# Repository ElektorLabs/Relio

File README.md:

# Relio
Relio : A Matter-Enabled Smart Controller for AC Appliances 
**Version:** v1  

## 📖 Project Overview

This project is a **Matter-enabled smart controller** built around the ESP32, with support for **relay control, environment sensing, energy monitoring, and occupancy detection**.  
It combines **hardware (KiCAD PCB design)** and **firmware (Arduino/C++ code)** into a single, ready-to-build system.

---

## 📂 Repository Structure

```

├── hardware/      # KiCAD PCB design files (schematics & layout)
└── src/           # Source code (Arduino / ESP-IDF compatible)

````

---

## ⚙️ Features

- **3x On/Off Lights** 💡  
  Controlled through a TCA9554 I²C expander.  
  - Always start **OFF** when powered up (safe startup).  
  - Exposed as **separate Matter endpoints**.  

- **Environmental Sensing (BME688)** 🌡️💧  
  - Temperature & Humidity exposed to Matter.  
  - Pressure & Gas Resistance logged to Serial for debugging.  

- **Energy Monitoring (BL0942)** ⚡  
  - Measures Voltage, Current, Power, Energy, Frequency.  
  - Data shown in Serial logs (Watts/Current can later be exposed to Matter).  

- **Occupancy Detection** 🚶‍♂️  
  - Uses TCA9554 pin 0 as input.  
  - HIGH = Occupied, LOW = Not Occupied.  
  - Reflected in Matter occupancy endpoint.  

- **Commissioning & Control** 🔐  
  - Commission into Matter fabric with QR/Manual code.  
  - BOOT button short press = toggle Light 1.  
  - BOOT button long press (5s) = decommission node.  

---

## 🧑‍💻 How the Code Works

- **Relay Control:**  
  `SWITCH1/2/3` booleans track relay states. Callbacks ensure Matter state and hardware (TCA9554 relays) stay in sync.  

- **BME688:**  
  Reads real temperature/humidity every 5s → updates Matter.  
  Pressure/gas logged for debugging but not exposed to Matter (yet).  

- **BL0942:**  
  Runs on `Serial1` (pins RX=4, TX=5, 4800 baud). Provides live power metrics to Serial monitor.  

- **Occupancy:**  
  Directly read from **TCA9554 pin 0**. When state changes, it’s pushed to the Matter controller and printed to Serial.  

---

## 🚀 Getting Started

1. Clone this repo:  
   ```bash
   git clone https://github.com/ElektorLabs/Relio.git
2. Open the src/ folder in Arduino IDE or PlatformIO.

3. Install dependencies:

   * [Espressif Matter Arduino](https://github.com/espressif/arduino-esp32)
   * [TCA9554 library](https://github.com/RobTillaart/TCA9554)
   * [BL0942 library](https://github.com/santerilindfors/BL0942)
   * [BME688 library](https://github.com/styropyr0/BME688)

4. Upload the code to your ESP32.

5. Use your Matter controller app to commission the device.

## 🛠️ Future Work

* Expose BL0942 **Power/Current** as native Matter attributes.
* Add Matter endpoints for **Pressure** & **Gas Resistance**.
* Add **configurable boot behavior** (restore last state vs always OFF).

---

## ⚠️ Disclaimer

This project is provided **as-is**, without warranty of any kind.
⚡ **Caution:** This project involves **mains-level voltages** (relays, energy metering).
Only experienced users should build or test this hardware. Always follow **electrical safety best practices** when working with AC-powered circuits.

The author is **not responsible** for any damage, injury, or loss caused by misuse of this code or hardware.

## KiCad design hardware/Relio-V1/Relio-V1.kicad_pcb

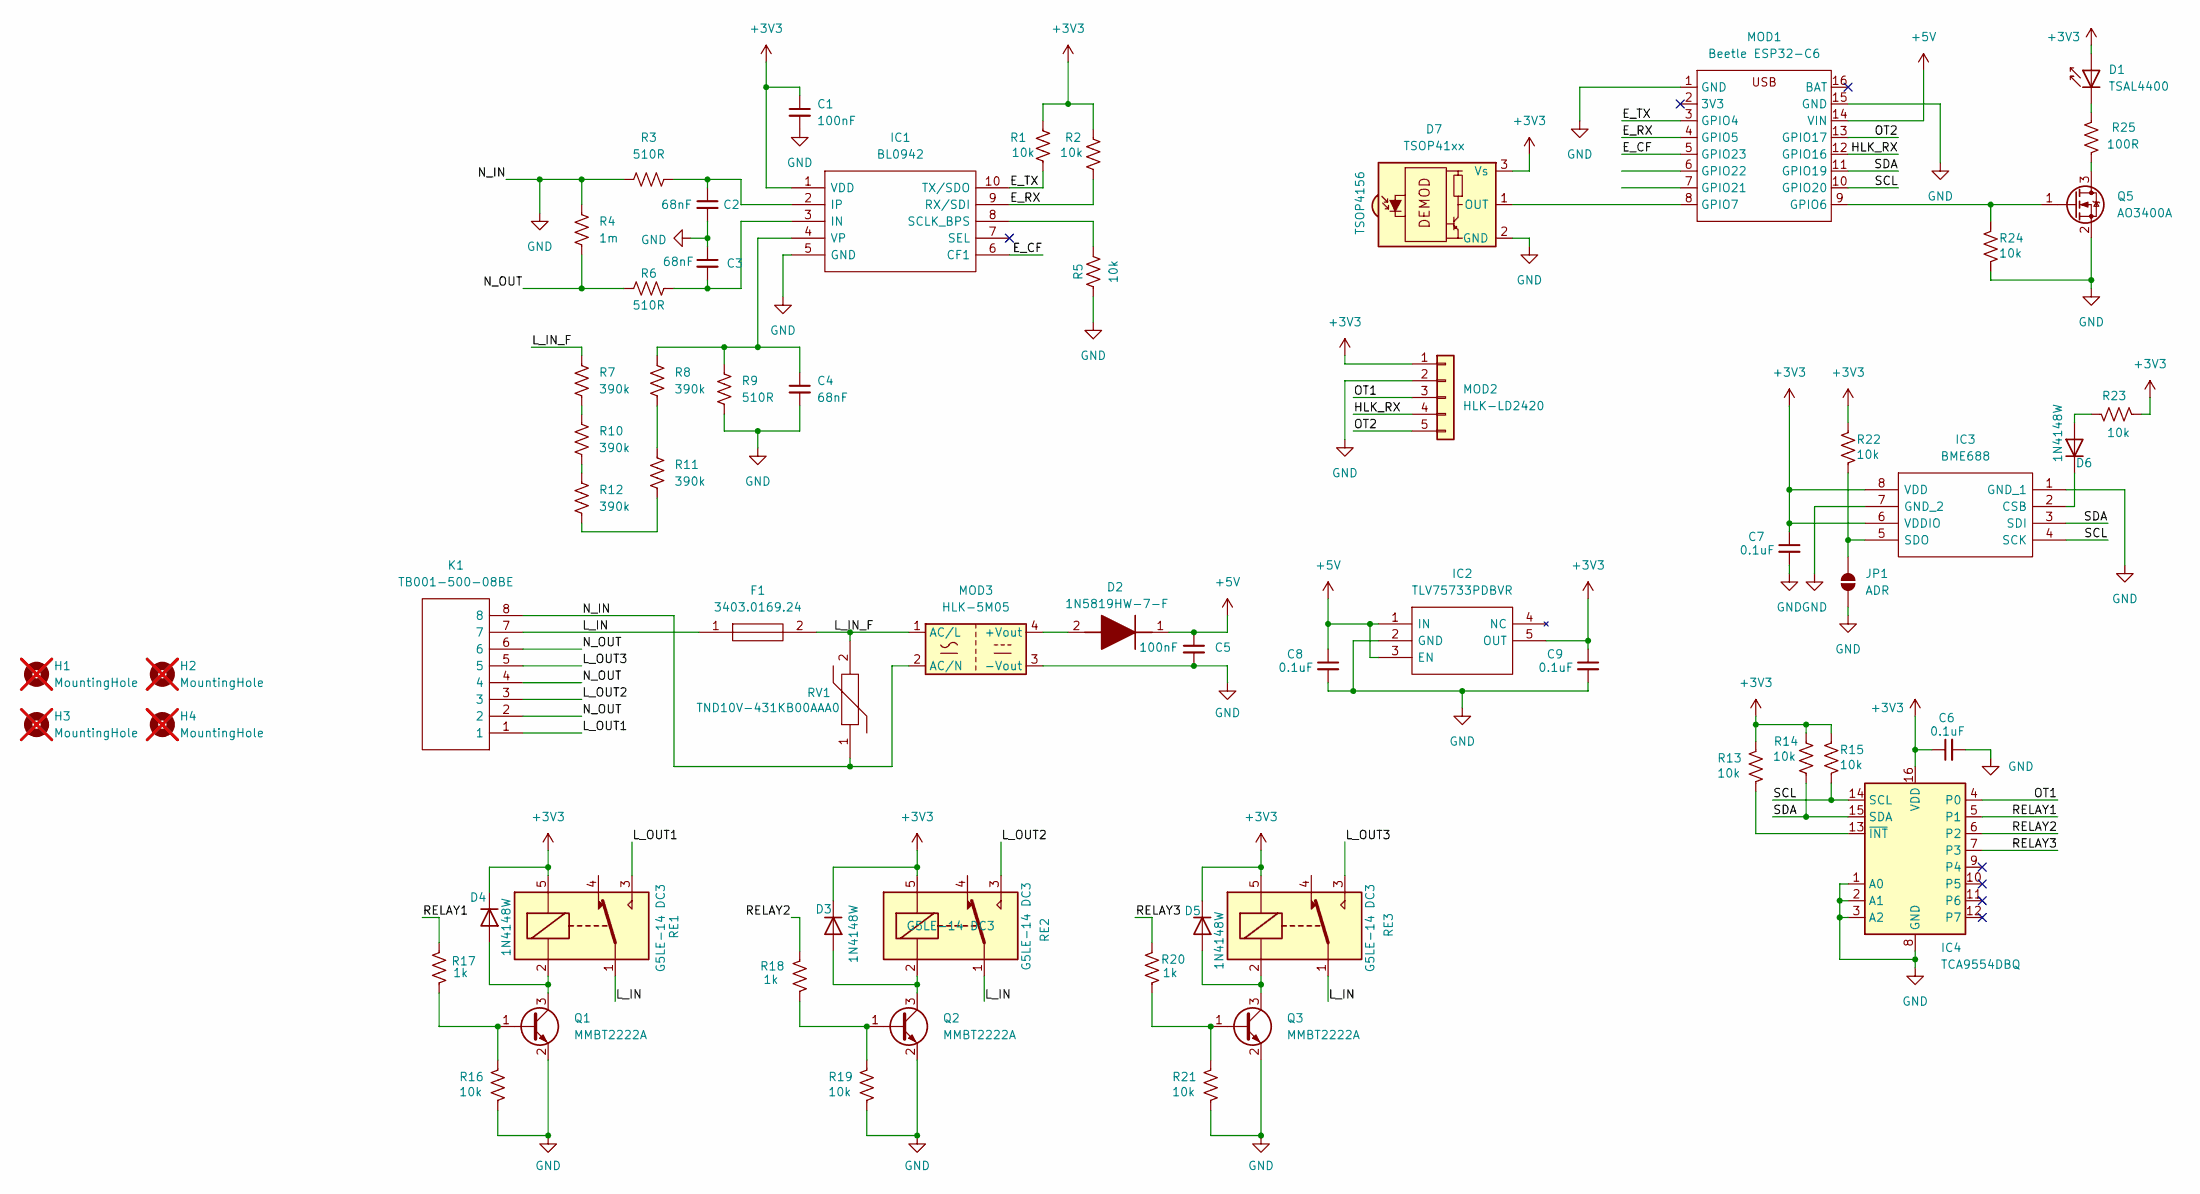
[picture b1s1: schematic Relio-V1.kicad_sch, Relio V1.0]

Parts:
C1, C5: 100nF; C_0805_2012Metric_Pad1.18x1.45mm_HandSolder; Manufacturer_Part_Number C0805C104M3RAC
C2, C3, C4: 68nF; C_0805_2012Metric_Pad1.18x1.45mm_HandSolder; Manufacturer_Part_Number C0805C683KARACAUTO
C6, C7, C8, C9: 0.1uF; C_0805_2012Metric_Pad1.18x1.45mm_HandSolder; Manufacturer_Part_Number C0805C104M3RAC
D1: TSAL4400; LED_D3.0mm_IRBlack; Manufacturer_Part_Number TSAL4400
D2: 1N5819HW-7-F; SOD3716X145N; Mouser Part Number 621-1N5819HW-F
D3, D4, D5, D6: 1N4148W; D_SOD-123; Manufacturer_Part_Number 1N4148W
D7: TSOP41xx; Vishay_MINICAST-3Pin; Manufacturer_Part_Number TSOP4156
F1: 3403.0169.24; FUSC10130X300N; Mouser Part Number 693-3403.0169.24
H1, H2, H3, H4: MountingHole; MountingHole_3.2mm_M3; not fitted
IC1: BL0942; SOP50P490X110-10N; Manufacturer_Part_Number BL0942
IC2: TLV75733PDBVR; SOT95P280X145-5N; Mouser Part Number 595-TLV75733PDBVR
IC3: BME688; Mouser Part Number 262-BME688
IC4: TCA9554DBQ; SSOP-16_3.9x4.9mm_P0.635mm; Manufacturer_Part_Number TCA9554DBQ
JP1: ADR; SolderJumper-2_P1.3mm_Open_RoundedPad1.0x1.5mm
K1: TB001-500-08BE; TB00150008BE; Mouser Part Number 490-TB001-500-08BE
MOD1: Beetle ESP32-C6; Manufacturer_Part_Number Beetle ESP32-C6
MOD2: HLK-LD2420; PinHeader_1x05_P2.54mm_Vertical; Manufacturer_Part_Number HLK-LD2420
MOD3: HLK-5M05; Converter_ACDC_Hi-Link_HLK-5Mxx; Manufacturer_Part_Number HLK-5M05
Q1, Q2, Q3: MMBT2222A; SOT-23; Manufacturer_Part_Number MMBT2222A
Q5: AO3400A; SOT-23; Manufacturer_Part_Number AO3400A
R1, R2, R5, R13, R14, R15, R16, R19, R21, R22, R23, R24: 10k; R_0805_2012Metric_Pad1.20x1.40mm_HandSolder; Manufacturer_Part_Number 0805W8J0103T5E
R3, R6, R9: 510R; R_0805_2012Metric_Pad1.20x1.40mm_HandSolder; Manufacturer_Part_Number SDR10EZPF5100
R4: 1m; R_1210_3225Metric
R7, R8, R10, R11, R12: 390k; R_2010_5025Metric; Manufacturer_Part_Number CRGCQ2010F390K
R17, R18, R20: 1k; R_0805_2012Metric_Pad1.20x1.40mm_HandSolder; Manufacturer_Part_Number 0805W8J0102T5E
R25: 100R; R_0805_2012Metric_Pad1.20x1.40mm_HandSolder; Manufacturer_Part_Number 0805S8J0101T5E
RE1, RE2, RE3: G5LE-14 DC3; Relay_SPDT_Omron-G5LE-1; Manufacturer_Part_Number G5LE-14 DC3
RV1: TND10V-431KB00AAA0; TND10V431KB00AAA0; Manufacturer_Part_Number TND10V-431KB00AAA0

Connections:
+3V3: C1.1, C6.1, C7.1, C9.1, D1.2 (A), D3.1 (K), D4.1 (K), D5.1 (K), D7.3 (Vs), IC1.1 (VDD), IC2.5 (OUT), IC3.6 (VDDIO), IC3.8 (VDD), IC4.16 (VDD), MOD2.1, R1.1, R2.1, R13.1, R14.1, R15.1, R22.1, R23.1, RE1.5, RE2.5, RE3.5
+5V: C5.1, C8.1, D2.1 (K), IC2.1 (IN), IC2.3 (EN), MOD1.14 (VIN)
/E_CF: IC1.6 (CF1), MOD1.5 (GPIO23)
/E_RX: IC1.9 (RX/SDI), MOD1.4 (GPIO5), R2.2
/E_TX: IC1.10 (TX/SDO), MOD1.3 (GPIO4), R1.2
/HLK_RX: MOD1.12 (GPIO16), MOD2.4
/L_IN: F1.1, K1.7, RE1.1, RE2.1, RE3.1
/L_IN_F: F1.2, MOD3.1 (AC/L), R7.2, RV1.2
/L_OUT1: K1.1, RE1.3
/L_OUT2: K1.3, RE2.3
/L_OUT3: K1.5, RE3.3
/N_OUT: K1.2, K1.4, K1.6, R4.1, R6.1
/OT1: IC4.4 (P0), MOD2.3
/OT2: MOD1.13 (GPIO17), MOD2.5
/RELAY1: IC4.5 (P1), R17.2
/RELAY2: IC4.6 (P2), R18.2
/RELAY3: IC4.7 (P3), R20.2
/SCL: IC3.4 (SCK), IC4.14 (SCL), MOD1.10 (GPIO20), R15.2
/SDA: IC3.3 (SDI), IC4.15 (SDA), MOD1.11 (GPIO19), R14.2
GND: C1.2, C2.2, C3.1, C4.2, C5.2, C6.2, C7.2, C8.2, C9.2, D7.2 (GND), IC1.5 (GND), IC2.2 (GND), IC3.1 (GND_1), IC3.7 (GND_2), IC4.1 (A0), IC4.2 (A1), IC4.3 (A2), IC4.8 (GND), JP1.1 (A), K1.8, MOD1.1 (GND), MOD1.15 (GND), MOD2.2, MOD3.2 (AC/N), MOD3.3 (-Vout), Q1.2 (E), Q2.2 (E), Q3.2 (E), Q5.2 (S), R3.1, R4.2, R5.1, R9.1, R16.2, R19.2, R21.2, R24.2, RV1.1
unnamed: D1.1 (K), R25.1
unnamed: D2.2 (A), MOD3.4 (+Vout)
unnamed: D3.2 (A), Q2.3 (C), RE2.2
unnamed: D4.2 (A), Q1.3 (C), RE1.2
unnamed: D5.2 (A), Q3.3 (C), RE3.2
unnamed: D6.2 (A), R23.2
unnamed: D6.1 (K), IC3.2 (CSB)
unnamed: D7.1 (OUT), MOD1.8 (GPIO7)
unnamed: C3.2, IC1.3 (IN), R6.2
unnamed: C2.1, IC1.2 (IP), R3.2
unnamed: IC1.8 (SCLK_BPS), R5.2
unnamed: C4.1, IC1.4 (VP), R8.2, R9.2
unnamed: IC3.5 (SDO), JP1.2 (B), R22.2
unnamed: IC4.13 (~INT), R13.2
unnamed: MOD1.9 (GPIO6), Q5.1 (G), R24.1
unnamed: Q1.1 (B), R16.1, R17.1
unnamed: Q2.1 (B), R18.1, R19.1
unnamed: Q3.1 (B), R20.1, R21.1
unnamed: Q5.3 (D), R25.2
unnamed: R10.1, R12.1
unnamed: R7.1, R10.2
unnamed: R11.1, R12.2
unnamed: R8.1, R11.2

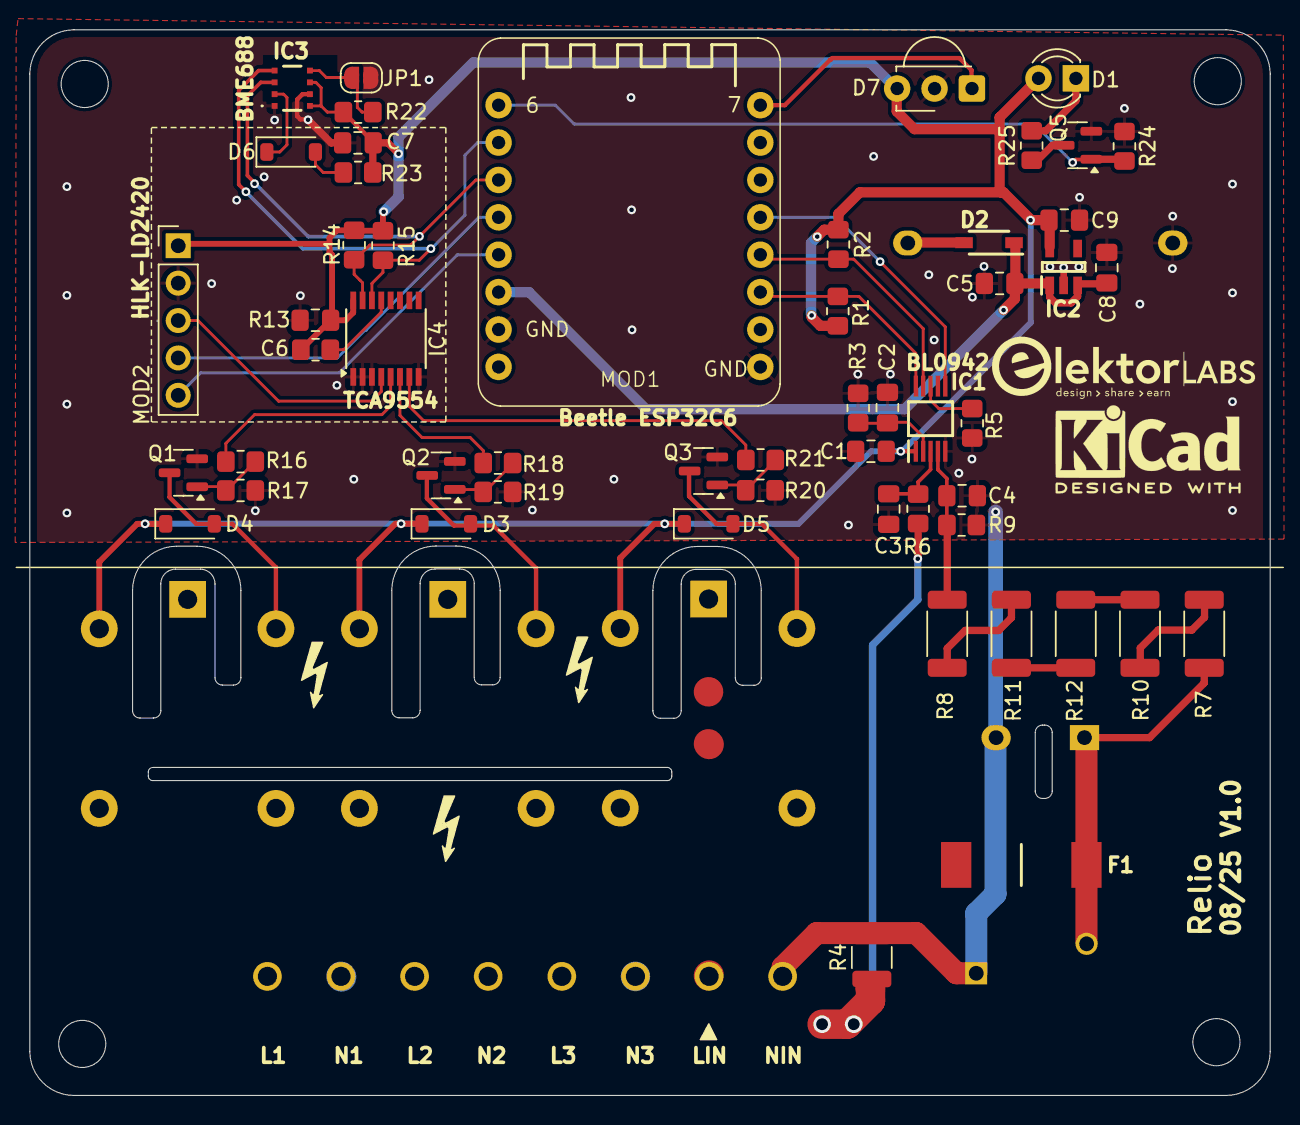
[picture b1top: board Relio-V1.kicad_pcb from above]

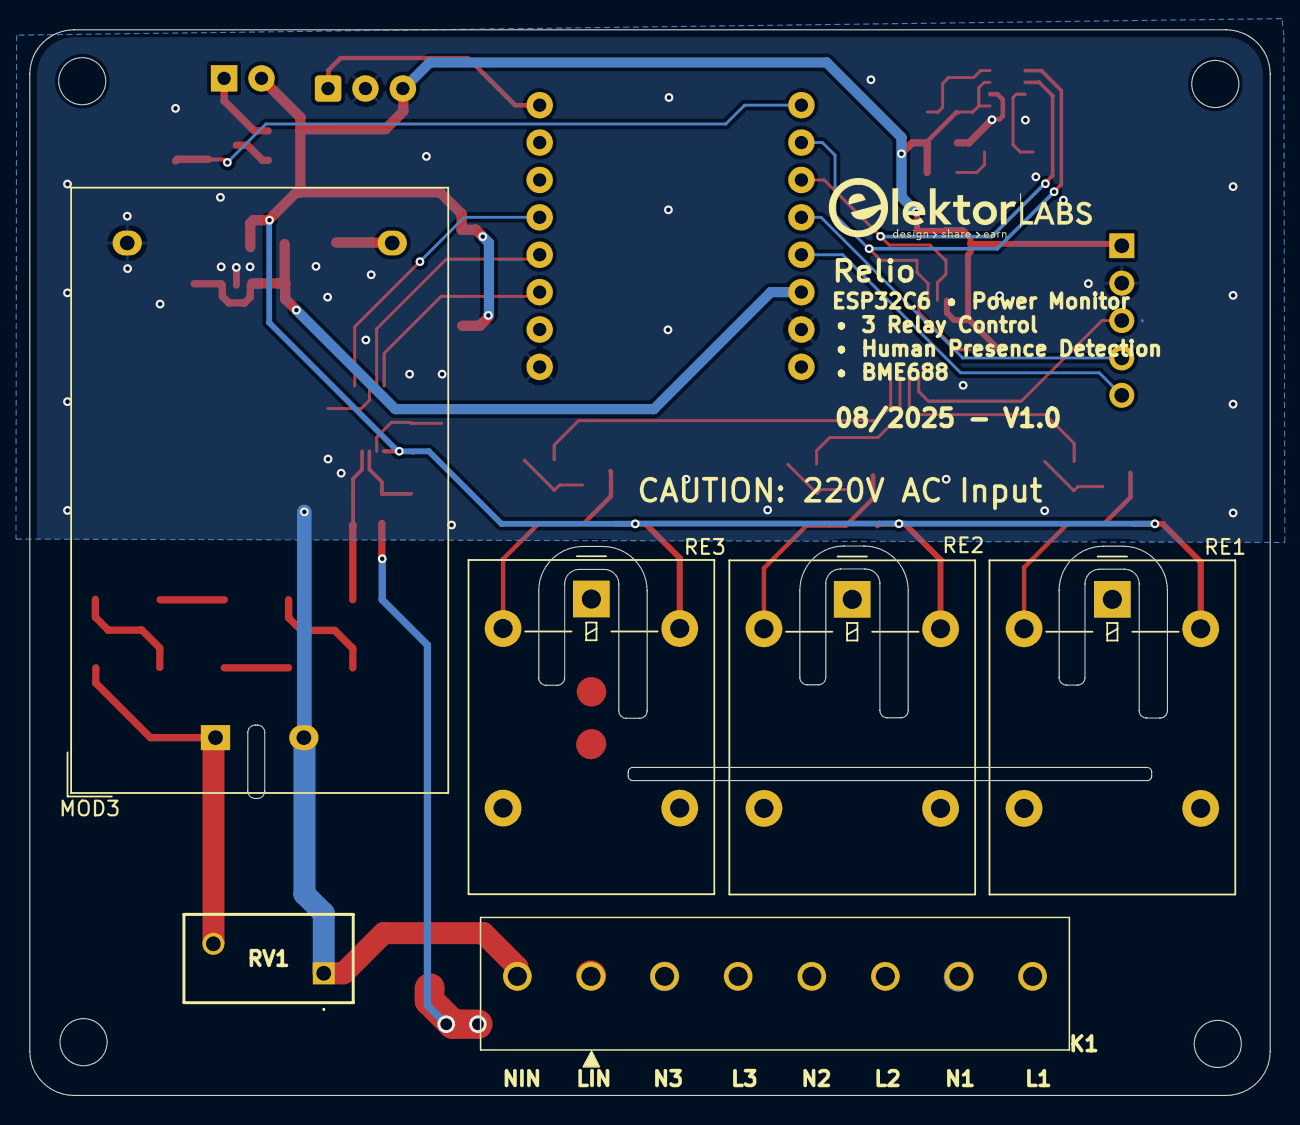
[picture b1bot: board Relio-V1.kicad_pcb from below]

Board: 2 copper layers, 84.3 x 72.4 mm, 63 parts (6 on the bottom side), 43 nets.

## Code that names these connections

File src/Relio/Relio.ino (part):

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const bool RELAY_ACTIVE_HIGH = true;  // set false if your relays are active-LOW

// Map switches to expander pins (0..7)
const uint8_t RELAY1_PIN = 1;
const uint8_t RELAY2_PIN = 2;
const uint8_t RELAY3_PIN = 3;

// ---------- BME688 (Temp/Humidity/Pressure/Gas) ----------
BME688 bme;        // I²C sensor at 0x76
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}

void applyAllRelaysFromState() {
  driveRelay(RELAY1_PIN, SWITCH1);
  driveRelay(RELAY2_PIN, SWITCH2);
  driveRelay(RELAY3_PIN, SWITCH3);
}

// ---------- Hard "All OFF on Boot" ----------
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  matterPref.putBool(kOnOffKey3, false);

  // Hardware OFF immediately (before Matter starts)
  driveRelay(RELAY1_PIN, false);
  driveRelay(RELAY2_PIN, false);
  driveRelay(RELAY3_PIN, false);
}

// ---------- On/Off callbacks (drive relays + persist) ----------
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  Serial.printf("Light 1 -> %s\r\n", state ? "ON" : "OFF");
  SWITCH1 = state;
  matterPref.putBool(kOnOffKey1, state);
  driveRelay(RELAY1_PIN, state);
  return true;
}
bool setLight2(bool state) {
  Serial.printf("Light 2 -> %s\r\n", state ? "ON" : "OFF");
  SWITCH2 = state;
  matterPref.putBool(kOnOffKey2, state);
  driveRelay(RELAY2_PIN, state);
  return true;
}
bool setLight3(bool state) {
  Serial.printf("Light 3 -> %s\r\n", state ? "ON" : "OFF");
  SWITCH3 = state;
  matterPref.putBool(kOnOffKey3, state);
  driveRelay(RELAY3_PIN, state);
  return true;
}

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
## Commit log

2025-08-19 added files
